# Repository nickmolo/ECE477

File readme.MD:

#Senior Design Project for Purdue ECE477
The following code is for a fabricated smart-watch for Senior design. Code in this repo is based off of various libraries including our own, such as the Adafruit Graphics Libraries for our SSD1351 display.

Midterm Design Review Presentation 
https://docs.google.com/presentation/d/1fQvJexct02s5zMMklutLdLCyOUqHS_1bk4CB7YSZFS4/edit?usp=sharing

Final Design Review Presentation
https://docs.google.com/presentation/d/1uoW5v5YpZROXi00Bag2v_5JE344Z9XPI0Cu_86e-bGs/edit?usp=sharing

Video!
https://www.youtube.com/watch?v=YeXBOrRXs24

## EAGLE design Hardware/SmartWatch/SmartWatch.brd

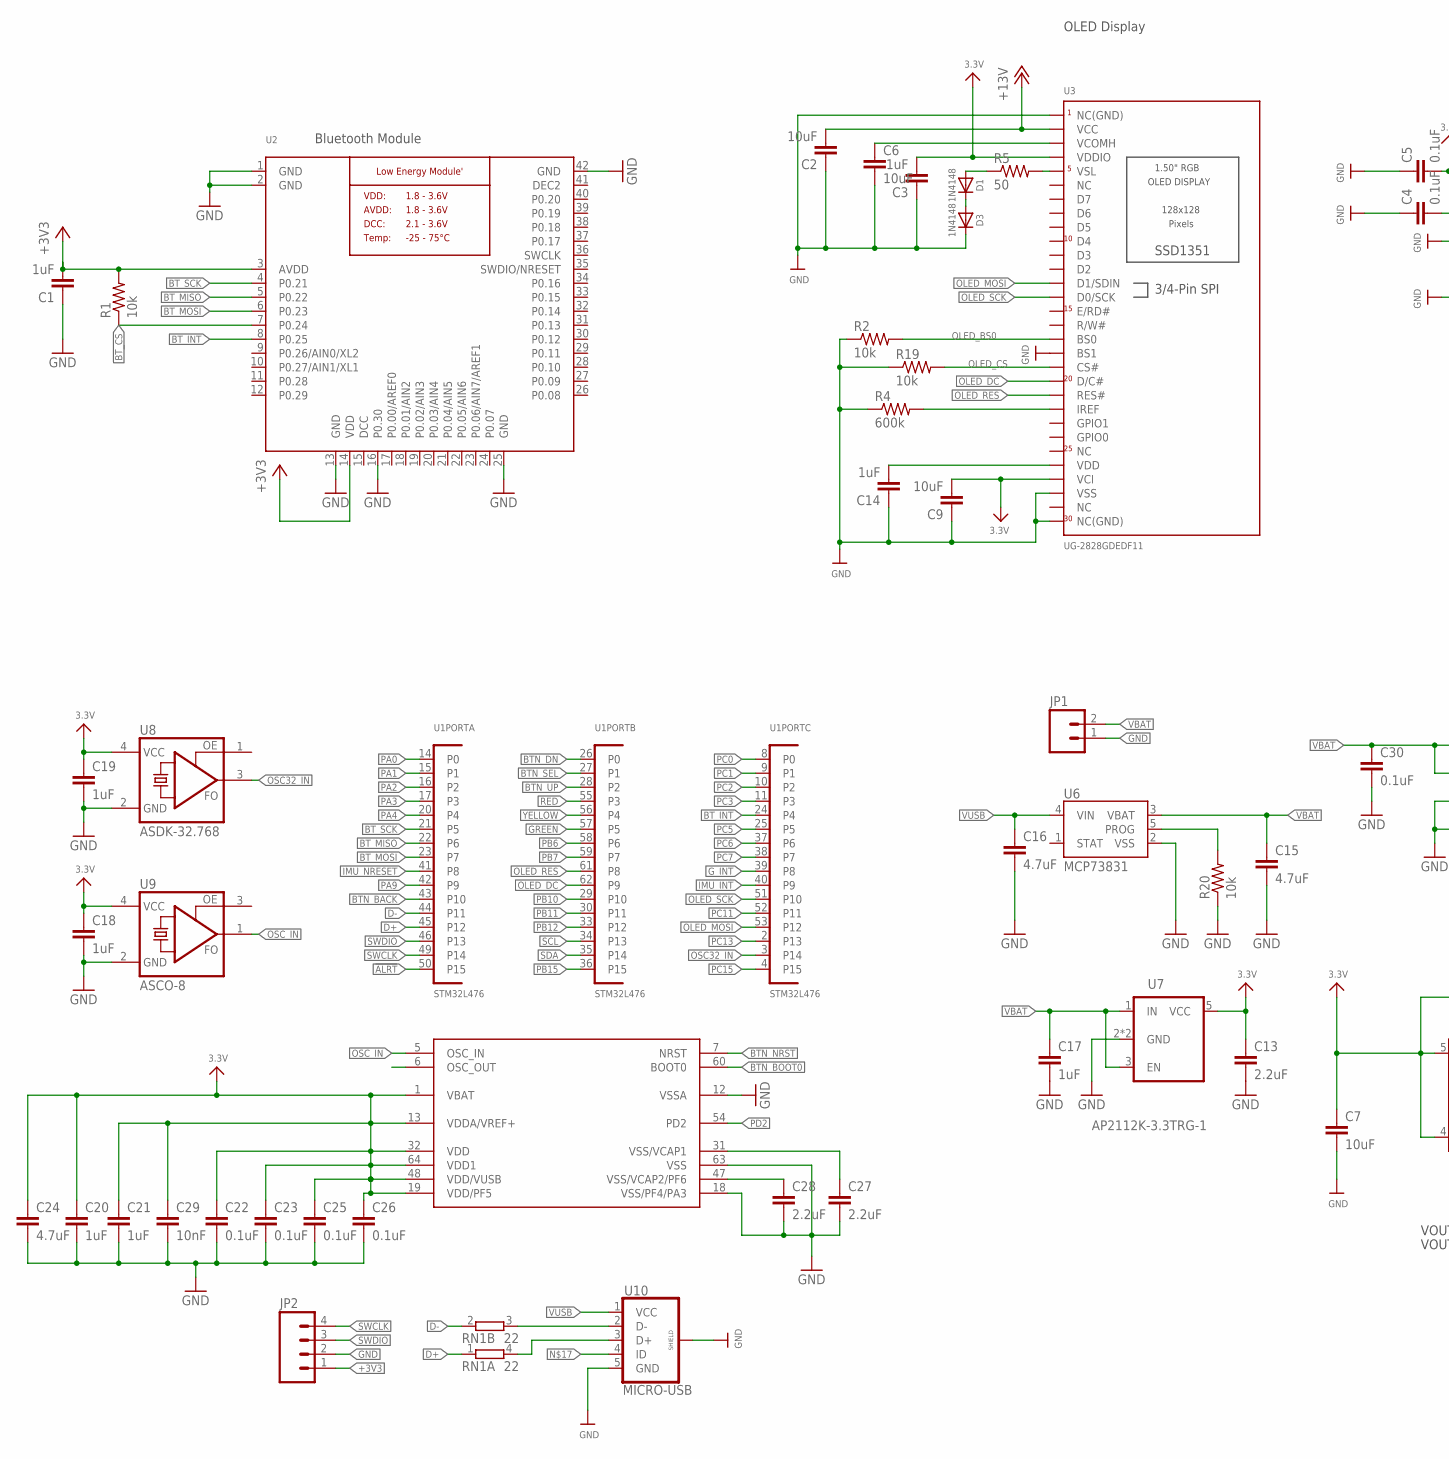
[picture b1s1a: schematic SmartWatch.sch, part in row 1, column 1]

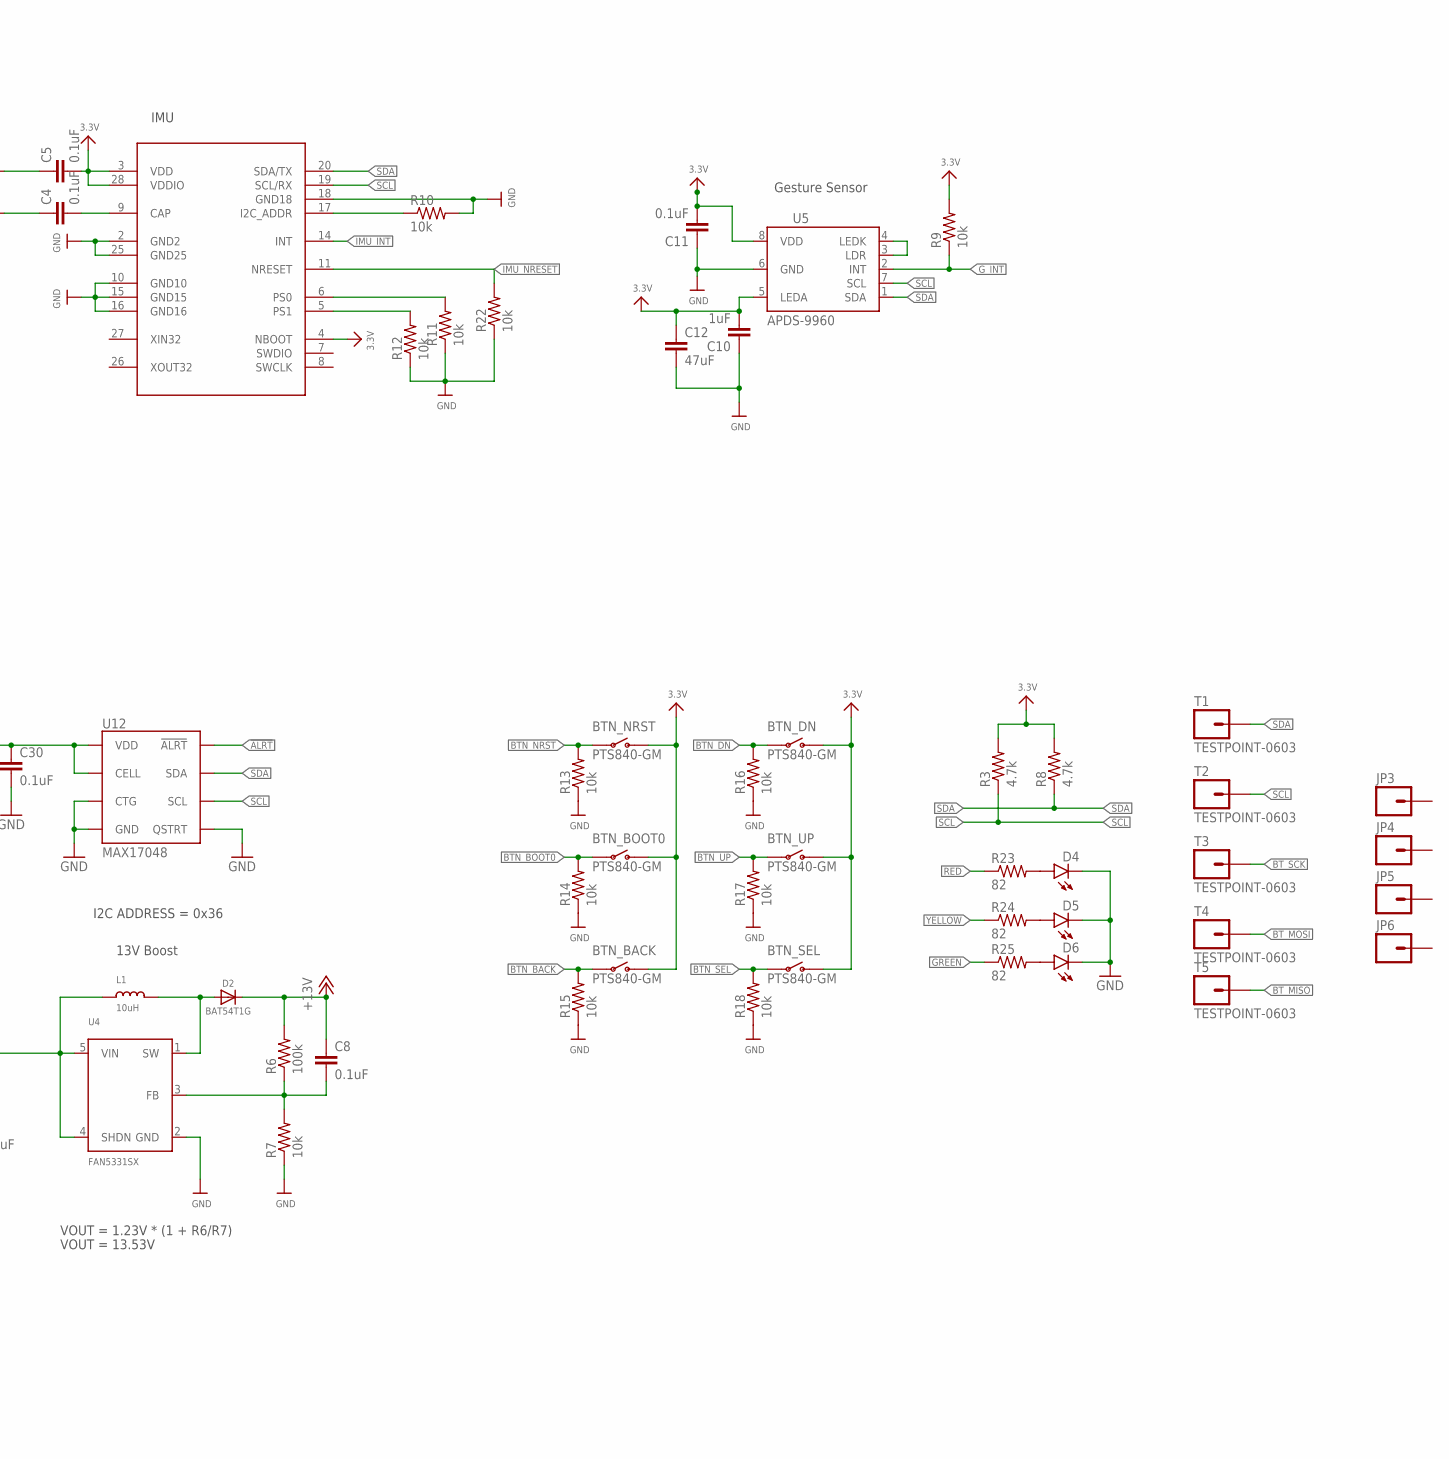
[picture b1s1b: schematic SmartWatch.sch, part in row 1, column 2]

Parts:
BTN_BACK: PTS840-GM
BTN_BOOT0: PTS840-GM
BTN_DN: PTS840-GM
BTN_NRST: PTS840-GM
BTN_SEL: PTS840-GM
BTN_UP: PTS840-GM
C1, C3, C10, C14, C17, C18, C19, C20, C21: 1uF; C0603
C2, C6, C7, C9: 10uF; C0603
C4, C5, C8, C11, C22, C23, C25, C26, C30: 0.1uF; C0603
C12: 47uF; C1206
C13, C27, C28: 2.2uF; C0603
C15, C16, C24: 4.7uF; C0603
C29: 10nF; C0603
D1, D3: 1N4148; SOD-323
D2: BAT54T1G; SOD-123
D4, D5, D6: LED0603; LED-0603
JP1: M021X02_NO_SILK; 1X02_NO_SILK
JP2: M04NO_SILK_ALL_ROUND; 1X04_NO_SILK_ALL_ROUND
JP3, JP4, JP5, JP6: M01PTH_NO_SILK_YES_STOP; 1X01_NO_SILK
L1: 10uH; INDUCTOR_1007
R1, R2, R7, R9, R10, R11, R12, R13, R14, R15, R16, R17, R18, R19, R20, R22: 10k; R0603
R3, R8: 4.7k; R0603
R4: 600k; R0603
R5: 50; R0603
R6: 100k; R0603
R23, R24, R25: 82; R0603
RN1: 22; EXBV4V
T1, T2, T3, T4, T5: TESTPOINT-0603
U1: STM32L476; TQFP64-10X10
U2: NRF51822_MODULE_MDBT40; BLE_MODULE_RAYTAC_MDBT40
U3: UG-2828GDEDF11; FPC_XF2M-3015-1A
U4: FAN5331SX; SOT23-5$1
U5: APDS-9960
U6: MCP73831; SOT23-5
U7: AP2112K-3.3TRG-1; SOT23-5
U8: ASDK-32.768
U9: ASCO-8
U10: MICRO-USB
U11: BNO055; LGA28
U12: MAX17048; DFN-8

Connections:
13V: C2.2, C8.1, D2.C, R6.2, U3.P$2 (VCC)
!ALRT: U1.50 (P15), U12.P$5 (!ALRT)
+3V3: BTN_BACK.3 (34), BTN_BACK.4 (34), BTN_BOOT0.3 (34), BTN_BOOT0.4 (34), BTN_DN.3 (34), BTN_DN.4 (34), BTN_NRST.3 (34), BTN_NRST.4 (34), BTN_SEL.3 (34), BTN_SEL.4 (34), BTN_UP.3 (34), BTN_UP.4 (34), C1.2, C3.2, C5.2, C7.1, C9.2, C10.2, C11.2, C12.1, C13.1, C18.1, C19.1, C20.1, C21.1, C22.1, C23.1, C24.1, C25.1, C26.1, C29.1, JP2.1, L1.P$1 (1), R1.2, R3.2, R8.2, R9.2, U1.1 (VBAT), U1.13 (VDDA/VREF+), U1.19 (VDD/PF5), U1.32 (VDD), U1.48 (VDD/VUSB), U1.64 (VDD1), U2.3 (AVDD), U2.14 (VDD), U3.P$4 (VDDIO), U3.P$27 (VCI), U4.4 (SHDN), U4.5 (VIN), U5.5 (LEDA), U5.8 (VDD), U7.5 (VCC), U8.4 (VCC), U9.4 (VCC), U11.3 (VDD), U11.4 (NBOOT), U11.28 (VDDIO)
BTN_BACK: BTN_BACK.1 (12), BTN_BACK.2 (12), R15.2, U1.43 (P10)
BTN_BOOT0: BTN_BOOT0.1 (12), BTN_BOOT0.2 (12), R14.2, U1.60 (BOOT0)
BTN_DN: BTN_DN.1 (12), BTN_DN.2 (12), R16.2, U1.26 (P0)
BTN_NRST: BTN_NRST.1 (12), BTN_NRST.2 (12), R13.2, U1.7 (NRST)
BTN_SEL: BTN_SEL.1 (12), BTN_SEL.2 (12), R18.2, U1.27 (P1)
BTN_UP: BTN_UP.1 (12), BTN_UP.2 (12), R17.2, U1.28 (P2)
BT_CS: R1.1, U2.7 (P0.24)
BT_INT: U1.24 (P4), U2.8 (P0.25)
BT_MISO: T5.1, U1.22 (P6), U2.5 (P0.22)
BT_MOSI: T4.1, U1.23 (P7), U2.6 (P0.23)
BT_SCK: T3.1, U1.21 (P5), U2.4 (P0.21)
D+: RN1.1, U1.45 (P12)
D-: RN1.2 (1), U1.44 (P11)
DCC: U2.15 (DCC)
DEC2: U2.41 (DEC2)
GND: C1.1, C2.1, C3.1, C4.1, C5.1, C6.2, C7.2, C9.1, C10.1, C11.1, C12.2, C13.2, C14.1, C15.2, C16.2, C17.2, C18.2, C19.2, C20.2, C21.2, C22.2, C23.2, C24.2, C25.2, C26.2, C27.2, C28.2, C29.2, C30.2, D3.C, D4.C, D5.C, D6.C, JP1.1, JP2.2, R2.1, R4.1, R7.1, R10.2, R11.1, R12.1, R13.1, R14.1, R15.1, R16.1, R17.1, R18.1, R19.1, R20.1, R22.1, U1.12 (VSSA), U1.18 (VSS/PF4/PA3), U1.63 (VSS), U2.1 (GND), U2.2 (GND), U2.13 (GND), U2.16 (P0.30), U2.25 (GND), U2.42 (GND), U3.P$1 (NC(GND)), U3.P$18 (BS1), U3.P$28 (VSS), U3.P$30 (NC(GND)), U4.2 (GND), U5.6 (GND), U6.2 (VSS), U7.2 (GND), U7.4 (GND), U8.2 (GND), U9.2 (GND), U10.5 (GND), U10.6 (SHIELD), U10.7 (SHIELD), U10.8 (SHIELD), U10.9 (SHIELD), U10.10 (SHIELD), U10.11 (SHIELD), U11.2 (GND2), U11.10 (GND10), U11.15 (GND15), U11.16 (GND16), U11.18 (GND18), U11.25 (GND25), U12.P$1 (CTG), U12.P$4 (GND), U12.P$6 (QSTRT), U12.P$9 (GND)
GREEN: R25.1, U1.57 (P5)
G_INT: R9.1, U1.39 (P8), U5.2 (INT)
ID: RN1.4 (2), U10.3 (D+)
IMU_INT: U1.40 (P9), U11.14 (INT)
IMU_NRESET: R22.2, U1.41 (P8), U11.11 (NRESET)
unnamed: R4.2, U3.P$22 (IREF)
unnamed: C14.2, U3.P$26 (VDD)
unnamed: R10.1, U11.17 (I2C_ADDR)
unnamed: C4.2, U11.9 (CAP)
unnamed: D2.A, L1.P$2 (2), U4.1 (SW)
unnamed: R5.2, U3.P$5 (VSL)
unnamed: D1.A, R5.1
unnamed: C8.2, R6.1, R7.2, U4.3 (FB)
unnamed: U5.3 (LDR), U5.4 (LEDK)
unnamed: RN1.3 (2), U10.2 (D-)
unnamed: D1.C, D3.A
unnamed: R12.2, U11.5 (PS1)
unnamed: R11.2, U11.6 (PS0)
unnamed: D4.A, R23.2
unnamed: D5.A, R24.2
unnamed: D6.A, R25.2
unnamed: C27.1, U1.31 (VSS/VCAP1)
unnamed: C28.1, U1.47 (VSS/VCAP2/PF6)
OLED_BS0: R2.2, U3.P$17 (BS0)
OLED_CS: R19.2, U3.P$19 (CS#)
OLED_DC: U1.62 (P9), U3.P$20 (D/C#)
OLED_MOSI: U1.53 (P12), U3.P$13 (D1/SDIN)
OLED_RES: U1.61 (P8), U3.P$21 (RES#)
OLED_SCK: U1.51 (P10), U3.P$14 (D0/SCK)
OSC32_IN: U1.3 (P14), U8.3 (FO)
OSC_IN: U1.5 (OSC_IN), U9.1 (FO)
PA0: U1.14 (P0)
PA1: U1.15 (P1)
PA2: U1.16 (P2)
PA3: U1.17 (P3)
PA4: U1.20 (P4)
PA9: U1.42 (P9)
PB6: U1.58 (P6)
PB7: U1.59 (P7)
PB10: U1.29 (P10)
PB11: U1.30 (P11)
PB12: U1.33 (P12)
PB15: U1.36 (P15)
PC0: U1.8 (P0)
PC1: U1.9 (P1)
PC2: U1.10 (P2)
PC3: U1.11 (P3)
PC5: U1.25 (P5)
PC6: U1.37 (P6)
PC7: U1.38 (P7)
PC11: U1.52 (P11)
PC13: U1.2 (P13)
PC15: U1.4 (P15)
PD2: U1.54 (PD2)
PROG: R20.2, U6.5 (PROG)
RED: R23.1, U1.55 (P3)
SCL: R3.1, T2.1, U1.34 (P13), U5.7 (SCL), U11.19 (SCL/RX), U12.P$7 (SCL)
SDA: R8.1, T1.1, U1.35 (P14), U5.1 (SDA), U11.20 (SDA/TX), U12.P$8 (SDA)
SWCLK: JP2.4, U1.49 (P14)
SWDIO: JP2.3, U1.46 (P13)
VBAT: C15.1, C17.1, C30.1, JP1.2, U6.3 (VBAT), U7.1 (IN), U7.3 (EN), U12.P$2 (CELL), U12.P$3 (VDD)
VCOMH1: C6.1, U3.P$3 (VCOMH)
VUSB: C16.1, U6.4 (VIN), U10.1 (VCC)
YELLOW: R24.1, U1.56 (P4)

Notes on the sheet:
VOUT = 1.23V * (1 + R6/R7)
VOUT = 13.53V
13V Boost
OLED Display
Bluetooth Module
IMU
Gesture Sensor
I2C ADDRESS = 0x36

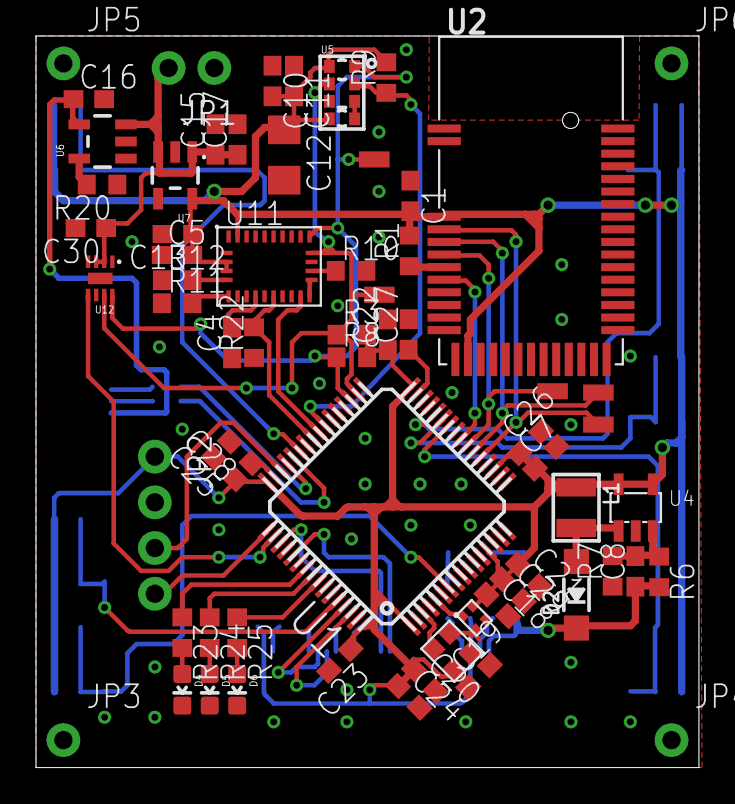
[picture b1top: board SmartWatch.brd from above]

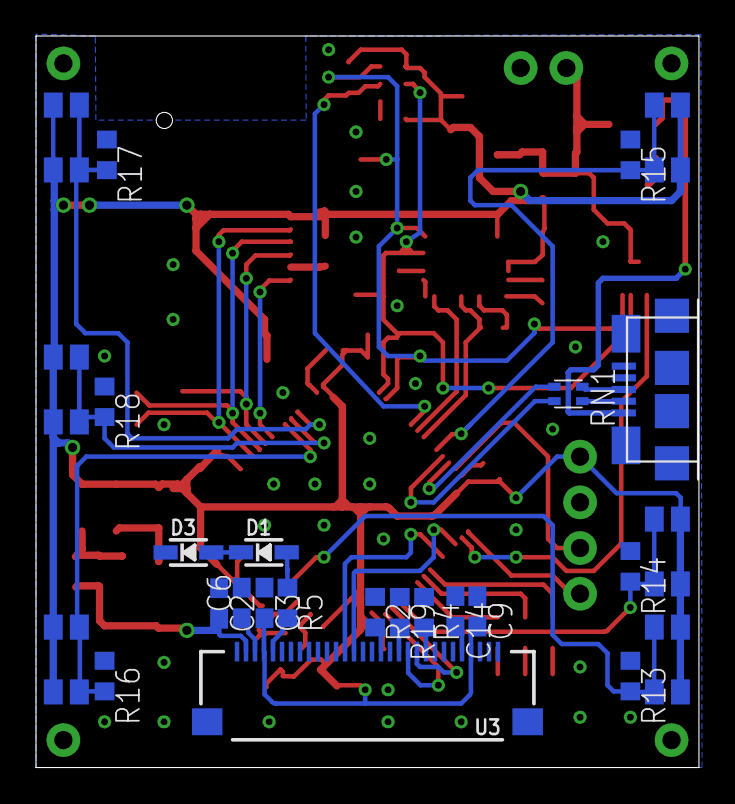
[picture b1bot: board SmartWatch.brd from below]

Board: 2 copper layers, 36.8 x 40.6 mm, 91 parts (26 on the bottom side), 58 nets.

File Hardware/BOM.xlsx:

Qty | Qty x6 | Qty to Buy | Value | Device | Package | Parts | Description | Supplier | Part Number
6 | 36 | 40 | PTS840-GM | PTS840-GM | PTS840-GM | BTN_BACK, BTN_BOOT0, BTN_DN, BTN_NRST, BTN_SEL, BTN_UP | Button | Digikey | CKN10507CT-ND
8 | 48 | 100 | 1uF | C-EUC0603 | C0603 | C1, C3, C10, C14, C17, C18, C19, C20, C21 | Capacitor | Digikey | 445-1604-1-ND
1 | 6 | 10 | 47uF | C-EUC1206 | C1206 | C12 | Capacitor | Digikey | 587-1780-1-ND
3 | 18 | 30 | 2.2uF | C-EUC0603 | C0603 | C13, C27, C28 | Capacitor | Digikey | 1276-1188-1-ND
3 | 18 | 100 | 4.7uF | C-EUC0603 | C0603 | C15, C16, C24 | Capacitor | Digikey | 1276-2087-1-ND
4 | 24 | 30 | 10uF | C-EUC0603 | C0603 | C2, C6, C7, C9 | Capacitor | Digikey | 445-9065-1-ND
1 | 6 | 10 | 10nF | C-EUC0603 | C0603 | C29 | Capacitor | Digikey | 445-1304-1-ND
8 | 48 | 100 | 0.1uF | C-EUC0603 | C0603 | C4, C5, C8, C11, C22, C23, C25, C26 | Capacitor | Digikey | 1276-1936-1-ND
2 | 12 | 20 | 1N4148 | DIODESOD-323 | SOD-323 | D1, D3 | Diode | Digikey | 1N4148WFL-G3-08GICT-ND
1 | 6 | 10 | BAT54T1G | DIODESOD-123 | SOD-123 | D2 | Diode | Digikey | BAT54T1GOSCT-ND
1 | 6 |  |  | M02PTH | 1X02 | JP1 | Standard 2-pin 0.1 " | Digikey
1 | 6 | 10 | 10uH | INDUCTOR | INDUCTOR_1007 | L1 | Inductors | Digikey | 587-1936-1-ND
17 | 102 | 500 | 10k | R-US_R0603 | R0603 | R1, R2, R7, R9, R10, R11, R12, R13, R14, R15, R16, R17, R18, R19, R20, R21, R22 | Resistor | Digikey | P10KGCT-ND50
2 | 12 | 100 | 4.7k | R-US_R0603 | R0603 | R3, R8 | Resistor | Digikey | P4.7KGCT-ND
1 | 6 | 50 | 600k | R-US_R0603 | R0603 | R4 | Resistor | Digikey | P604KHCT-ND
1 | 6 | 50 | 50 | R-US_R0603 | R0603 | R5 | Resistor | Digikey | P49.9HCT-ND
1 | 6 | 50 | 100k | R-US_R0603 | R0603 | R6 | Resistor | Digikey | P100KGCT-ND
1 | 6 | 10 | 22 | 2R-NEXBV4V | EXBV4V | RN1 | Array Chip Resistor | Digikey | Y2220CT-ND
1 | 6 | 5 | STM32L476 | STM32L476 | TQFP64-10X10 | U1 | Micro Controller | Digikey | 497-15877-ND
1 | 6 | 10 | MICRO-USB | MICRO-USB | MICRO-USB | U10 | USB Connector | Digikey | 609-4613-1-ND
1 | 6 |  | BNO055 | BNO055 | LGA28 | U11 | IMU | Mouser | 262-BNO055
1 | 6 |  |  | NRF51822_MODULE_MDBT40 | BLE_MODULE_RAYTAC_MDBT40 | U2 | nRF51822 Bluetooth | Adafruit | 2633
1 | 6 |  | UG-2828GDEDF11 | DISP_OLED_UG-2828GDEDF11BOTTOM | FPC_XF2M-3015-1A | U3 | OLED Display + zif!!! | BuyDisplay | ER-OLED015-1C
1 | 6 | 10 | FAN5331SX | FAN5331 | SOT23-5$1 | U4 | Boost Converter | Digikey | FAN5331SXCT-ND
1 | 6 | 5 | APDS-9960 | APDS-9960 | APDS-9960 | U5 | Gesture Sensor | Mouser | 630-APDS-9960
1 | 6 | 10 | MCP73831 | MCP73831 | SOT23-5 | U6 | Battery Charger | Digikey | MCP73831T-2ACI/OTCT-ND
1 | 6 | 10 | AP2112K-3.3TRG-1 | LDO-TPS78233 | SOT23-5 | U7 | Voltage Regulator | Digikey | AP2112K-3.3TRG1DICT-ND
1 | 6 | 6 | ASDK-32.768 | ASDK-32.768 | ASDK-32.768 | U8 | Oscillator | Digikey | 535-9999-1-ND
1 | 6 | 6 | ASCO-8 | ASCO-8 | ASCO-8 | U9 | Oscillator | Digikey | 535-12077-1-ND
5 | 30 | 30 |  | Test Point | 603 | T1, T2, T3, T4, T5 | Test point | Digikey | 571-1625854-3
5 | 30 |  |  | MAX17048G | TDFN-8 | U12 | Battery Monitor | Mouser | 700-MAX17048G+
3 | 18 |  | 82 | Resistor | 603 | R23, R24, R25 | Resistor | Digikey | P82GCT-ND
1 | 6 |  | RED | LED | 603 | D4 | Red LED | Digikey | 475-2506-1-ND
1 | 6 |  | YELLOW | LED | 603 | D5 | Yellow LED | Digikey | 475-1196-1-ND
1 | 6 |  | GREEN | LED | 603 | D6 | Green LED | Digikey | 475-2709-1-ND

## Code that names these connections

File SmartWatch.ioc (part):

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Mcu.Name=STM32L476R(C-E-G)Tx
Mcu.Package=LQFP64
Mcu.UserName=STM32L476RGTx
PA10.GPIOParameters=GPIO_Label
PA10.GPIO_Label=BTN_BACK
PA10.Signal=GPIO_Input
PA11.GPIOParameters=GPIO_Label
PA11.GPIO_Label=USB_D-
PA11.Mode=Device_Only
PA11.Signal=USB_OTG_FS_DM
PA12.GPIOParameters=GPIO_Label
PA12.GPIO_Label=USB_D+
PA12.Mode=Device_Only
PA12.Signal=USB_OTG_FS_DP
PA13.GPIOParameters=GPIO_Label
PA13.GPIO_Label=SWDIO
PA13.Mode=Serial-Wire
PA13.Signal=SYS_JTMS-SWDIO
PA14.GPIOParameters=GPIO_Label
PA14.GPIO_Label=SWCLK
PA14.Mode=Serial-Wire
PA14.Signal=SYS_JTCK-SWCLK
PA15.GPIOParameters=GPIO_Label
PA15.GPIO_Label=\!ALRT
PA15.Signal=GPIO_Input
PA5.GPIOParameters=GPIO_Label
PA5.GPIO_Label=BT_SCK
PA5.Mode=Full_Duplex_Master
PA5.Signal=SPI1_SCK
PA6.GPIOParameters=GPIO_Label
PA6.GPIO_Label=BT_MISO
PA6.Mode=Full_Duplex_Master
PA6.Signal=SPI1_MISO
PA7.GPIOParameters=GPIO_Label
PA7.GPIO_Label=BT_MOSI
PA7.Mode=Full_Duplex_Master
PA7.Signal=SPI1_MOSI
PA8.GPIOParameters=GPIO_Label
PA8.GPIO_Label=IMU_NRESET
PA8.Signal=GPIO_Output
PB0.GPIOParameters=GPIO_Label
PB0.GPIO_Label=BTN_DN
PB0.Signal=GPIO_Input
PB1.GPIOParameters=GPIO_Label
PB1.GPIO_Label=BTN_SEL
PB1.Signal=GPIO_Input
PB13.GPIOParameters=GPIO_Label
PB13.GPIO_Label=SCL
PB13.Mode=I2C
PB13.Signal=I2C2_SCL
PB14.GPIOParameters=GPIO_Label
PB14.GPIO_Label=SDA
PB14.Mode=I2C
PB14.Signal=I2C2_SDA
PB2.GPIOParameters=GPIO_Label
PB2.GPIO_Label=BTN_UP
PB2.Signal=GPIO_Input
PB3.GPIOParameters=GPIO_Label
PB3.GPIO_Label=RED
PB3.Signal=GPIO_Output
PB4.GPIOParameters=GPIO_Label
PB4.GPIO_Label=YELLOW
PB4.Signal=GPIO_Output
PB5.GPIOParameters=GPIO_Label
PB5.GPIO_Label=GREEN
PB5.Signal=GPIO_Output
PB8.GPIOParameters=GPIO_Label
PB8.GPIO_Label=OLED_RES
PB8.Signal=GPIO_Output
PB9.GPIOParameters=GPIO_Label
PB9.GPIO_Label=OLED_DC
PB9.Signal=GPIO_Output
PC10.GPIOParameters=GPIO_Label
PC10.GPIO_Label=OLED_SCK
PC10.Mode=TX_Only_Simplex_Unidirect_Master
PC10.Signal=SPI3_SCK
PC12.GPIOParameters=GPIO_Label
PC12.GPIO_Label=OLED_MOSI
PC12.Mode=TX_Only_Simplex_Unidirect_Master
PC12.Signal=SPI3_MOSI
PC14/OSC32_IN.GPIOParameters=GPIO_Label
PC14/OSC32_IN.GPIO_Label=OSC32_IN
PC14/OSC32_IN.Mode=LSE-External-Clock-Source
PC14/OSC32_IN.Signal=RCC_OSC32_IN
PC4.GPIOParameters=GPIO_Label
PC4.GPIO_Label=BT_INT
PC4.Signal=GPIO_Input
PC8.GPIOParameters=GPIO_Label
PC8.GPIO_Label=G_INT
PC8.Signal=GPIO_Input
PC9.GPIOParameters=GPIO_Label
PC9.GPIO_Label=IMU_INT
PC9.Signal=GPIO_Input
PH0/OSC_IN.GPIOParameters=GPIO_Label
PH0/OSC_IN.GPIO_Label=OSC_IN
PH0/OSC_IN.Mode=HSE-External-Clock-Source
PH0/OSC_IN.Signal=RCC_OSC_IN
RCC.HSE_VALUE=8000000
RCC.SYSCLKFreq_VALUE=80000000
RCC.SYSCLKSource=RCC_SYSCLKSOURCE_PLLCLK

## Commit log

2015-08-31 adding readme
2015-09-21 Adding Eagle gitignore and start of schematic
2015-09-22 adding start of libraries, schematic and board files
2015-09-22 adding things to library
2015-09-23 adding micro board lbr
2015-09-23 Continued work on schematic and libraries
2015-09-23 renamed part
2015-09-23 Updated schematic
2015-09-23 added to schematic more
2015-09-23 created usb part
2015-09-26 hardware updates
2015-09-26 added almost all parts, changed power management IC
2015-09-26 finished schematic!
2015-09-26 started board layout
2015-09-26 adding stm32cubemx updated fike
2015-09-26 finished PCB and added images
2015-09-26 cropped image of pcb
2015-09-27 updated with ext programming port also eliminated some gnd loops and added text
2015-09-28 added mounting holes
2015-09-28 changed mounting holes to pin headers
2015-09-29 update board
2015-09-30 added test points and icreased keepout around bluetooth
2015-09-30 updated pcb and bom with test points
2015-10-05 added leds, need to figure out which pins they go to
2015-10-07 finished schematic
2015-10-07 finished pcb made gerbers
2015-10-07 Added software so far for Screen
2015-10-07 Updated readme\?
2015-10-16 updated PCB to 1.1 and added battery monitoring chip
2015-10-16 adding images
2015-10-16 shrunk some images
2015-10-16 adding more images and such
2015-10-16 fixed airwire
2015-10-16 added presentation link to readme
2015-10-21 added decoupling capacitor
2015-10-21 added updated cam files
2015-10-21 updated bom
2015-10-23 adding actual gerber files
2015-10-23 fixed sparkfun cam file
2015-10-23 updated zip file to final
2015-10-26 added new cam file and updated gerbers
2015-11-01 adding working hal library to start development for
2015-11-04 Updated dispaly code
2015-11-04 Added bluetooth code
2015-11-04 Fixed add
2015-11-09 adding bin file
2015-11-10 removes compiled libs
2015-11-10 adding main bin
2015-12-02 adding led test project
2015-12-03 adding test code
2015-12-03 more makefiles not working
2015-12-06 adding pdf of schematic
2015-12-07 Added GCC Compile-ready oled display code

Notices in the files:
parts and their libraries:
SparkFun-Sensors: Licensing: Creative Commons ShareAlike 4.0 International - https://creativecommons.org/licenses/by-sa/4.0
SparkFun-DigitalIC: Licensing: CC v3.0 Share-Alike You are welcome to use this library for commercial purposes.
